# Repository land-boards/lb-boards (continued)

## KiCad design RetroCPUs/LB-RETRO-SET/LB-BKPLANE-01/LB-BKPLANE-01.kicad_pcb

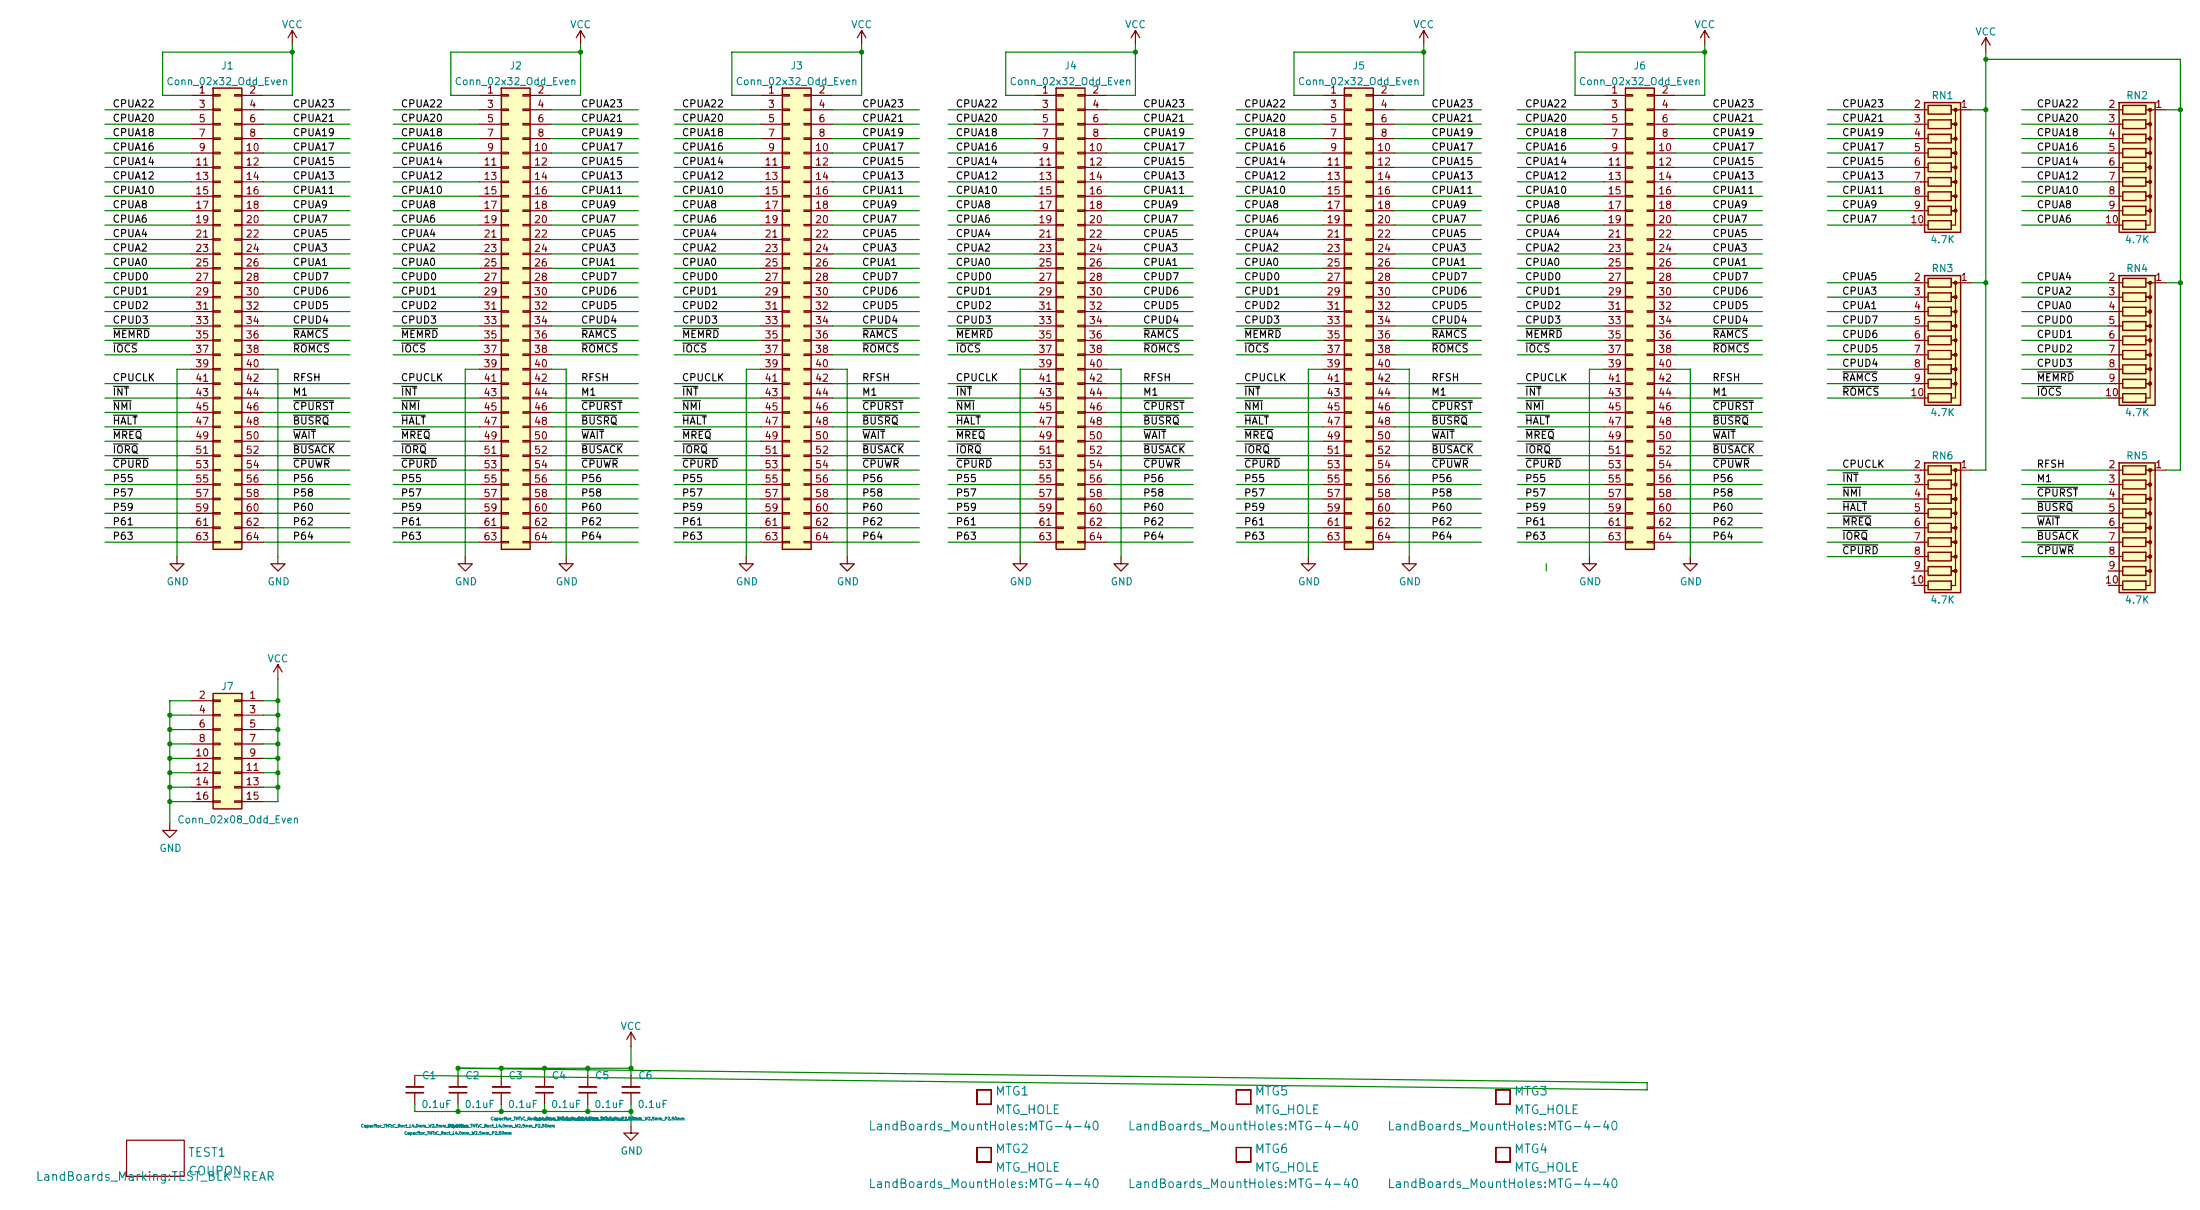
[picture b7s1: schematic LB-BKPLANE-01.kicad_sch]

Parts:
C1, C2, C3, C4, C5, C6: 0.1uF; C_Rect_L4.0mm_W2.5mm_P2.50mm
J1, J2, J3, J4, J5, J6: Conn_02x32_Odd_Even; PinHeader_2x32_P2.54mm_Vertical
J7: Conn_02x08_Odd_Even; PinHeader_2x08_P2.54mm_Vertical
MTG1, MTG2, MTG3, MTG4, MTG5, MTG6: MTG_HOLE; MTG-4-40
RN1, RN2, RN3, RN4, RN5, RN6: 4.7K; R_Array_SIP10
TEST1: COUPON; TEST_BLK-REAR

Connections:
/CPUA0: J1.25, J2.25, J3.25, J4.25, J5.25, J6.25, RN4.4 (R3)
/CPUA1: J1.26, J2.26, J3.26, J4.26, J5.26, J6.26, RN3.4 (R3)
/CPUA2: J1.23, J2.23, J3.23, J4.23, J5.23, J6.23, RN4.3 (R2)
/CPUA3: J1.24, J2.24, J3.24, J4.24, J5.24, J6.24, RN3.3 (R2)
/CPUA4: J1.21, J2.21, J3.21, J4.21, J5.21, J6.21, RN4.2 (R1)
/CPUA5: J1.22, J2.22, J3.22, J4.22, J5.22, J6.22, RN3.2 (R1)
/CPUA6: J1.19, J2.19, J3.19, J4.19, J5.19, J6.19, RN2.10 (R9)
/CPUA7: J1.20, J2.20, J3.20, J4.20, J5.20, J6.20, RN1.10 (R9)
/CPUA8: J1.17, J2.17, J3.17, J4.17, J5.17, J6.17, RN2.9 (R8)
/CPUA9: J1.18, J2.18, J3.18, J4.18, J5.18, J6.18, RN1.9 (R8)
/CPUA10: J1.15, J2.15, J3.15, J4.15, J5.15, J6.15, RN2.8 (R7)
/CPUA11: J1.16, J2.16, J3.16, J4.16, J5.16, J6.16, RN1.8 (R7)
/CPUA12: J1.13, J2.13, J3.13, J4.13, J5.13, J6.13, RN2.7 (R6)
/CPUA13: J1.14, J2.14, J3.14, J4.14, J5.14, J6.14, RN1.7 (R6)
/CPUA14: J1.11, J2.11, J3.11, J4.11, J5.11, J6.11, RN2.6 (R5)
/CPUA15: J1.12, J2.12, J3.12, J4.12, J5.12, J6.12, RN1.6 (R5)
/CPUA16: J1.9, J2.9, J3.9, J4.9, J5.9, J6.9, RN2.5 (R4)
/CPUA17: J1.10, J2.10, J3.10, J4.10, J5.10, J6.10, RN1.5 (R4)
/CPUA18: J1.7, J2.7, J3.7, J4.7, J5.7, J6.7, RN2.4 (R3)
/CPUA19: J1.8, J2.8, J3.8, J4.8, J5.8, J6.8, RN1.4 (R3)
/CPUA20: J1.5, J2.5, J3.5, J4.5, J5.5, J6.5, RN2.3 (R2)
/CPUA21: J1.6, J2.6, J3.6, J4.6, J5.6, J6.6, RN1.3 (R2)
/CPUA22: J1.3, J2.3, J3.3, J4.3, J5.3, J6.3, RN2.2 (R1)
/CPUA23: J1.4, J2.4, J3.4, J4.4, J5.4, J6.4, RN1.2 (R1)
/CPUCLK: J1.41, J2.41, J3.41, J4.41, J5.41, J6.41, RN6.2 (R1)
/CPUD0: J1.27, J2.27, J3.27, J4.27, J5.27, J6.27, RN4.5 (R4)
/CPUD1: J1.29, J2.29, J3.29, J4.29, J5.29, J6.29, RN4.6 (R5)
/CPUD2: J1.31, J2.31, J3.31, J4.31, J5.31, J6.31, RN4.7 (R6)
/CPUD3: J1.33, J2.33, J3.33, J4.33, J5.33, J6.33, RN4.8 (R7)
/CPUD4: J1.34, J2.34, J3.34, J4.34, J5.34, J6.34, RN3.8 (R7)
/CPUD5: J1.32, J2.32, J3.32, J4.32, J5.32, J6.32, RN3.7 (R6)
/CPUD6: J1.30, J2.30, J3.30, J4.30, J5.30, J6.30, RN3.6 (R5)
/CPUD7: J1.28, J2.28, J3.28, J4.28, J5.28, J6.28, RN3.5 (R4)
/M1: J1.44, J2.44, J3.44, J4.44, J5.44, J6.44, RN5.3 (R2)
/P55: J1.55, J2.55, J3.55, J4.55, J5.55, J6.55
/P56: J1.56, J2.56, J3.56, J4.56, J5.56, J6.56
/P57: J1.57, J2.57, J3.57, J4.57, J5.57, J6.57
/P58: J1.58, J2.58, J3.58, J4.58, J5.58, J6.58
/P59: J1.59, J2.59, J3.59, J4.59, J5.59, J6.59
/P60: J1.60, J2.60, J3.60, J4.60, J5.60, J6.60
/P61: J1.61, J2.61, J3.61, J4.61, J5.61, J6.61
/P62: J1.62, J2.62, J3.62, J4.62, J5.62, J6.62
/P63: J1.63, J2.63, J3.63, J4.63, J5.63, J6.63
/P64: J1.64, J2.64, J3.64, J4.64, J5.64, J6.64
/RFSH: J1.42, J2.42, J3.42, J4.42, J5.42, J6.42, RN5.2 (R1)
/~BUSACK: J1.52, J2.52, J3.52, J4.52, J5.52, J6.52, RN5.7 (R6)
/~BUSRQ: J1.48, J2.48, J3.48, J4.48, J5.48, J6.48, RN5.5 (R4)
/~CPURD: J1.53, J2.53, J3.53, J4.53, J5.53, J6.53, RN6.8 (R7)
/~CPURST: J1.46, J2.46, J3.46, J4.46, J5.46, J6.46, RN5.4 (R3)
/~CPUWR: J1.54, J2.54, J3.54, J4.54, J5.54, J6.54, RN5.8 (R7)
/~HALT: J1.47, J2.47, J3.47, J4.47, J5.47, J6.47, RN6.5 (R4)
/~INT: J1.43, J2.43, J3.43, J4.43, J5.43, J6.43, RN6.3 (R2)
/~IOCS: J1.37, J2.37, J3.37, J4.37, J5.37, J6.37, RN4.10 (R9)
/~IORQ: J1.51, J2.51, J3.51, J4.51, J5.51, J6.51, RN6.7 (R6)
/~MEMRD: J1.35, J2.35, J3.35, J4.35, J5.35, J6.35, RN4.9 (R8)
/~MREQ: J1.49, J2.49, J3.49, J4.49, J5.49, J6.49, RN6.6 (R5)
/~NMI: J1.45, J2.45, J3.45, J4.45, J5.45, J6.45, RN6.4 (R3)
/~RAMCS: J1.36, J2.36, J3.36, J4.36, J5.36, J6.36, RN3.9 (R8)
/~ROMCS: J1.38, J2.38, J3.38, J4.38, J5.38, J6.38, RN3.10 (R9)
/~WAIT: J1.50, J2.50, J3.50, J4.50, J5.50, J6.50, RN5.6 (R5)
GND: C1.1, C2.1, C3.1, C4.1, C5.1, C6.1, J1.39, J1.40, J2.39, J2.40, J3.39, J3.40, J4.39, J4.40, J5.39, J5.40, J6.39, J6.40, J7.2, J7.4, J7.6, J7.8, J7.10, J7.12, J7.14, J7.16
VCC: C1.2, C2.2, C3.2, C4.2, C5.2, C6.2, J1.1, J1.2, J2.1, J2.2, J3.1, J3.2, J4.1, J4.2, J5.1, J5.2, J6.1, J6.2, J7.1, J7.3, J7.5, J7.7, J7.9, J7.11, J7.13, J7.15, RN1.1 (common), RN2.1 (common), RN3.1 (common), RN4.1 (common), RN5.1 (common), RN6.1 (common)

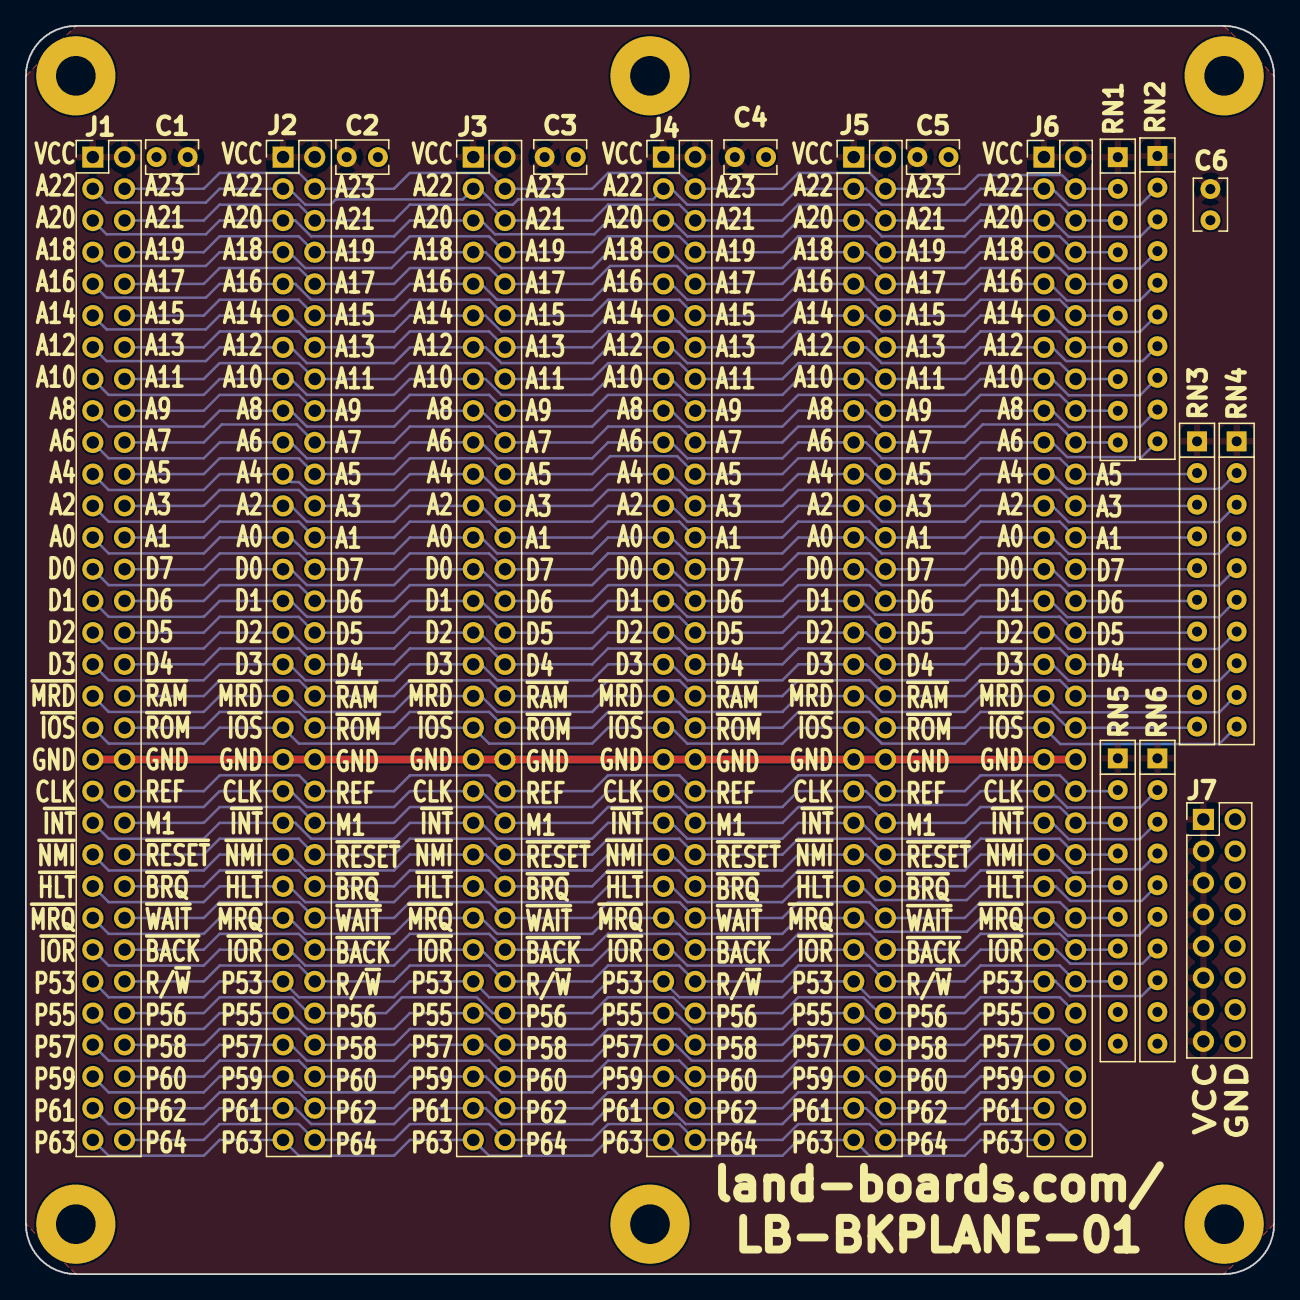
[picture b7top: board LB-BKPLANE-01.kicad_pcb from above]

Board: 2 copper layers, 100.0 x 100.0 mm, 26 parts (0 on the bottom side), 62 nets.

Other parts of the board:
TEST: COUPON; TEST_BLK-REAR
